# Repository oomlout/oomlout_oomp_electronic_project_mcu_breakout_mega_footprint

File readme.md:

# MCU Breakout Mega Footprint
An MCU Breakout Mega Footprint.
## notes 
### steps
* make the modules
* draw the modules
* incorporate in schematic
* make pcb
* make into footprint
### included footprints  
* arduino nano
  * kicad_module_arduino_nano_withmountingholes
* arduino pro mini 
  * sparkfun_boards_arduino_pro_mini
* raspberry pi pico 2040  
  * arturo182_module_extra_raspberrypi_pico  
* esp wroom 32 devkit c  
  * footprint espressif_espressif_esp32_devkitc  
An MCU Breakout Mega Footprint.  
* ibom github: [ibom github](kicad\current_version\working\bom\ibom.html)
* ibom direct: [ibom direct](https://raw.githack.com/oomlout/oomlout_oomp_electronic_project_mcu_breakout_mega_footprint/main/kicad/current_version/working/bom/ibom.html)

## schematic  
  
[schematic (pdf)](kicad/current_version/working/working_schematic.pdf)  

## pcb  

[board (pdf)](kicad/current_version/working/working.pdf)  

## corel working

## oomp_parts_summary
| index | designator | quantity | oomp_id | 
| --- | --- | --- | --- | 
| 1 | BB3 | 1 | electronic_breakout_board_devkitc_mcu_espressif_esp32 | 
| 2 | BB1 | 1 | electronic_breakout_board_pico_mcu_raspberry_pi_2040 | 
| 3 | BB2 | 1 | electronic_breakout_board_shennie_mcu_atmega328p_arduino_compatible | 

Search Links: (L) - lcsc, (D) - digikey, (M) - mouser, (N) - newark, (SZ) - szlcsc
note: a work on progress that takes the bom file from kicad pcb and try's to add oomp details

## positions
### top
| # Ref | Val | Package | PosX | PosY | Rot | Side | 
| --- | --- | --- | --- | --- | --- | --- | 
| BB1 | bbmcu_electronic_breakout_board_pico_mcu_raspberry_pi_2040 | bbmcu_electronic_breakout_board_pico_mcu_raspberry_pi_2040 | 60.96 | -71.12 | 0.0 | top | 
| BB2 | bbmcu_electronic_breakout_board_shennie_mcu_atmega328p | bbmcu_electronic_breakout_board_shennie_mcu_atmega328p_arduino_compatible | 57.15 | -44.3881 | 0.0 | top | 
| BB3 | bbmcu_electronic_breakout_board_devkitc_mcu_espressif_esp32 | bbmcu_electronic_breakout_board_devkitc_mcu_espressif_esp32 | 54.745 | -44.3881 | 0.0 | top | 

### bottom
no data

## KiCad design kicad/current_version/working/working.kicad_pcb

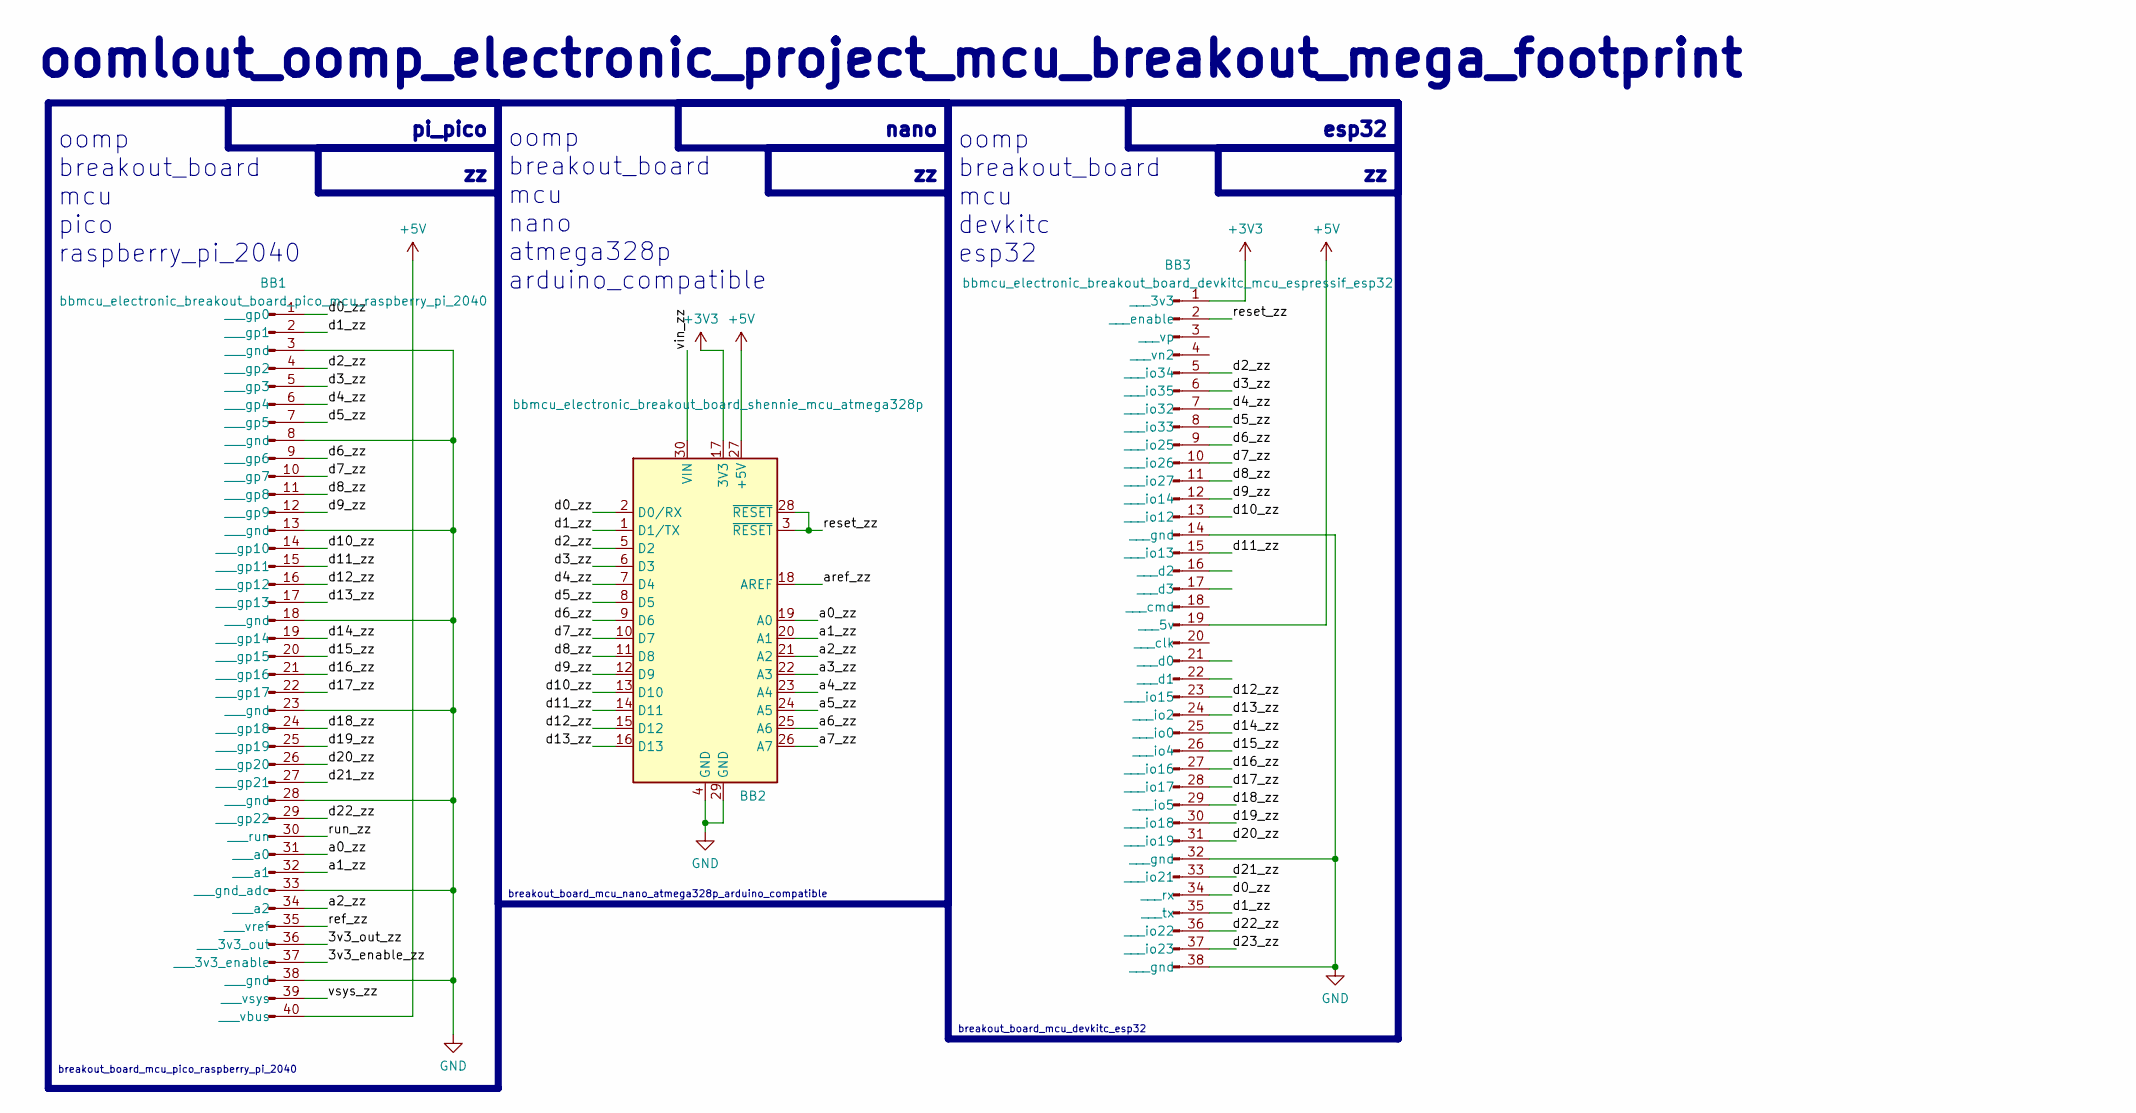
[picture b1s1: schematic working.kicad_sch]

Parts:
BB1: bbmcu_electronic_breakout_board_pico_mcu_raspberr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; bbmcu_electronic_breakout_board_pico_mcu_raspberry_pi_2040
BB2: bbmcu_electronic_breakout_board_shennie_mcu_atmeg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; bbmcu_electronic_breakout_board_shennie_mcu_atmega328p_ardu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
BB3: bbmcu_electronic_breakout_board_devkitc_mcu_espre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; bbmcu_electronic_breakout_board_devkitc_mcu_espressif_esp32

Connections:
+3V3: BB2.17 (3V3), BB3.1 (___3v3)
+5V: BB1.40 (___vbus), BB2.27 (+5V), BB3.19 (___5v)
/3v3_enable_zz: BB1.37 (___3v3_enable)
/3v3_out_zz: BB1.36 (___3v3_out)
/a0_zz: BB1.31 (___a0), BB2.19 (A0)
/a1_zz: BB1.32 (___a1), BB2.20 (A1)
/a2_zz: BB1.34 (___a2), BB2.21 (A2)
/a3_zz: BB2.22 (A3)
/a4_zz: BB2.23 (A4)
/a5_zz: BB2.24 (A5)
/a6_zz: BB2.25 (A6)
/a7_zz: BB2.26 (A7)
/aref_zz: BB2.18 (AREF)
/d0_zz: BB1.1 (___gp0), BB2.2 (D0/RX), BB3.34 (___rx)
/d1_zz: BB1.2 (___gp1), BB2.1 (D1/TX), BB3.35 (___tx)
/d2_zz: BB1.4 (___gp2), BB2.5 (D2), BB3.5 (___io34)
/d3_zz: BB1.5 (___gp3), BB2.6 (D3), BB3.6 (___io35)
/d4_zz: BB1.6 (___gp4), BB2.7 (D4), BB3.7 (___io32)
/d5_zz: BB1.7 (___gp5), BB2.8 (D5), BB3.8 (___io33)
/d6_zz: BB1.9 (___gp6), BB2.9 (D6), BB3.9 (___io25)
/d7_zz: BB1.10 (___gp7), BB2.10 (D7), BB3.10 (___io26)
/d8_zz: BB1.11 (___gp8), BB2.11 (D8), BB3.11 (___io27)
/d9_zz: BB1.12 (___gp9), BB2.12 (D9), BB3.12 (___io14)
/d10_zz: BB1.14 (___gp10), BB2.13 (D10), BB3.13 (___io12)
/d11_zz: BB1.15 (___gp11), BB2.14 (D11), BB3.15 (___io13)
/d12_zz: BB1.16 (___gp12), BB2.15 (D12), BB3.23 (___io15)
/d13_zz: BB1.17 (___gp13), BB2.16 (D13), BB3.24 (___io2)
/d14_zz: BB1.19 (___gp14), BB3.25 (___io0)
/d15_zz: BB1.20 (___gp15), BB3.26 (___io4)
/d16_zz: BB1.21 (___gp16), BB3.27 (___io16)
/d17_zz: BB1.22 (___gp17), BB3.28 (___io17)
/d18_zz: BB1.24 (___gp18), BB3.29 (___io5)
/d19_zz: BB1.25 (___gp19), BB3.30 (___io18)
/d20_zz: BB1.26 (___gp20), BB3.31 (___io19)
/d21_zz: BB1.27 (___gp21), BB3.33 (___io21)
/d22_zz: BB1.29 (___gp22), BB3.36 (___io22)
/d23_zz: BB3.37 (___io23)
/ref_zz: BB1.35 (___vref)
/reset_zz: BB2.3 (~RESET), BB2.28 (~RESET), BB3.2 (___enable)
/run_zz: BB1.30 (___run)
/vin_zz: BB2.30 (VIN)
/vsys_zz: BB1.39 (___vsys)
GND: BB1.3 (___gnd), BB1.8 (___gnd), BB1.13 (___gnd), BB1.18 (___gnd), BB1.23 (___gnd), BB1.28 (___gnd), BB1.33 (___gnd_adc), BB1.38 (___gnd), BB2.4 (GND), BB2.29 (GND), BB3.14 (___gnd), BB3.32 (___gnd), BB3.38 (___gnd)

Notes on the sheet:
oomlout_oomp_electronic_project_mcu_breakout_mega_footprint
oomp breakout_board mcu pico raspberry_pi_2040
nano
breakout_board_mcu_pico_raspberry_pi_2040
oomp breakout_board mcu nano atmega328p arduino_compatible
breakout_board_mcu_nano_atmega328p_arduino_compatible
pi_pico
breakout_board_mcu_devkitc_esp32
oomp breakout_board mcu devkitc esp32
esp32

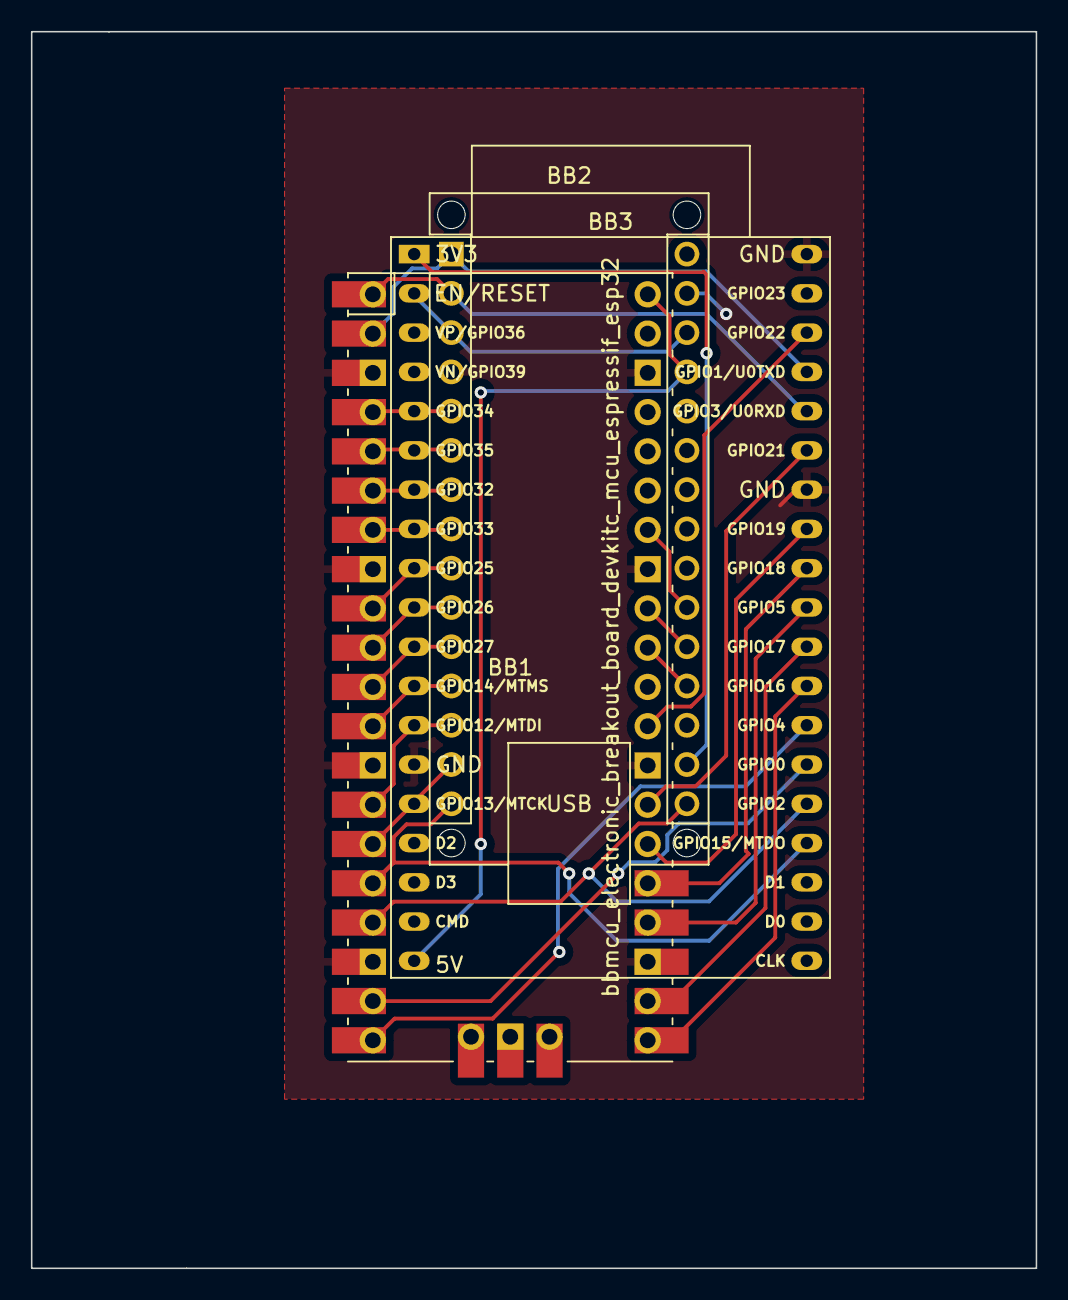
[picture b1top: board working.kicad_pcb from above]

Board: 2 copper layers, 65.0 x 80.0 mm, 3 parts (0 on the bottom side), 30 nets.

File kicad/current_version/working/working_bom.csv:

"Id";"Designator";"Footprint";"Quantity";"Designation";"Supplier and ref";
1;"BB3";"bbmcu_electronic_breakout_board_devkitc_mcu_espressif_esp32";1;"bbmcu_electronic_breakout_board_devkitc_mcu_espressif_esp32";;;
2;"BB1";"bbmcu_electronic_breakout_board_pico_mcu_raspberry_pi_2040";1;"bbmcu_electronic_breakout_board_pico_mcu_raspberry_pi_2040";;;
3;"BB2";"bbmcu_electronic_breakout_board_shennie_mcu_atmega328p_arduino_compatible";1;"bbmcu_electronic_breakout_board_shennie_mcu_atmega328p";;;

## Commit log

2023-09-20 initial work
2023-09-20 first works
2023-09-20 commiting after auto generation
